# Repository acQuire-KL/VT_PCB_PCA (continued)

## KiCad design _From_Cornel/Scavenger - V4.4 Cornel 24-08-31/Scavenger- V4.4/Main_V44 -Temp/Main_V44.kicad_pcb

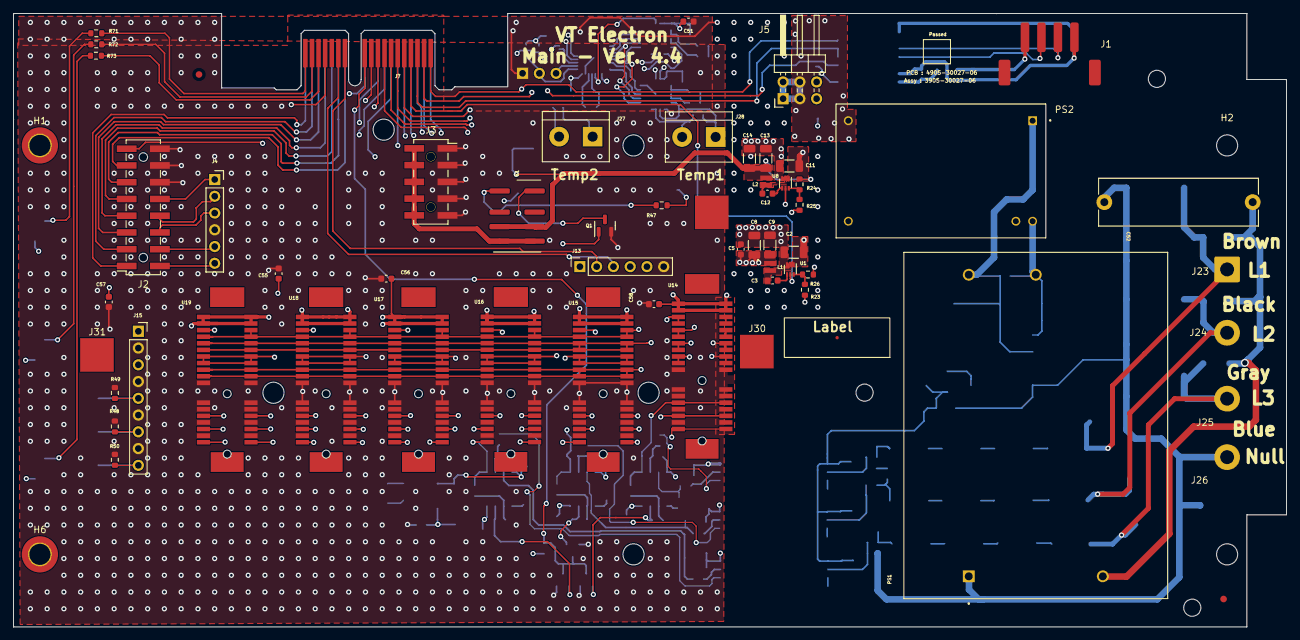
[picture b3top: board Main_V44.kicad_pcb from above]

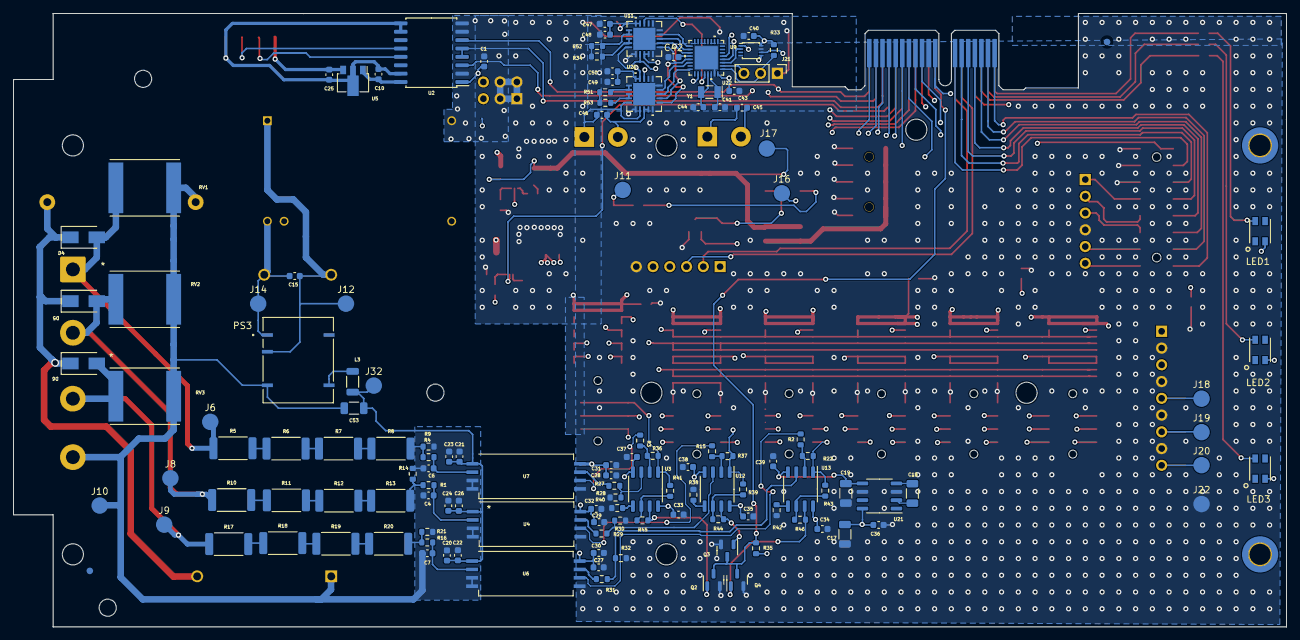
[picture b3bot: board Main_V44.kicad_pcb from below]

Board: 4 copper layers, 193.0 x 93.0 mm, 203 parts (131 on the bottom side), 138 nets.

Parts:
C1, C3, C5, C10, C12, C15, C20, C21, C24, C25, C27, C28, C29, C33, C34, C35, C36, C37, C38, C39, C40, C43, C47, C48, C49, C50, C55, C56, C57, C58: 100n; C_0603_1608Metric
C2, C11, C53: 10uF/16V; C_1206_3216Metric
C4, C6, C7: 1n; C_0603_1608Metric
C8, C9, C13, C14: 22uF/6,3V; C_1206_3216Metric
C17, C18, C19: 10u; C_1206_3216Metric
C22, C23, C26, C30, C31, C32: 1uF; C_0603_1608Metric
C41, C44: 10p; C_0603_1608Metric
C42: 1u; C_0603_1608Metric
C45, C46: 10n; C_0603_1608Metric
C51: 4,7n; C_0603_1608Metric
C52: F862DI224K310ZLH0J; C_Rect_L24.0mm_W7.0mm_P22.50mm_MKT
D4, D5, D6: BYG21M-E3/TR; D_SMA
FID1, FID2, FID3, FID4: Fiducial; Fiducial_1mm_Mask2mm
H1, H6: MountingHole; MountingHole_3.2mm_M3_ISO14580_Pad_TopBottom
H2, H3, H4, H5, H7, H8, H9, H10, H11, H12: MountingHole; MountingHole_3.2mm_M3
J1: Conn_01x04_Male; A2501-SR04-XH4AWB
J2: Conn_02x08_Counter_Clockwise; PinSocket_2x08_P2.54mm_Vertical_SMD_MOD
J3: Conn_02x05_Counter_Clockwise; PinSocket_2x05_P2.54mm_Vertical_SMD
J4, J13: Conn_01x06_Female; PinSocket_1x06_P2.54mm_Vertical
J5: DS1022-2*10RF11x3; PinHeader_2x03_P2.54mm_Horizontal
J6, J8, J9, J10, J11, J12, J14, J16, J17, J18, J19, J20, J22, J32: Conn_01x01_Female; TestPoint_DELTA
J7: Bus_PCI_Express_x1_MOD; BUS_PCIexpress_x1
J15: DS1002-03-1*36131(9); PinSocket_1x09_P2.54mm_Vertical
J21: Conn_01x03_Male; PinHeader_1x03_P2.54mm_Vertical
J23: Conn_01x01_Female; DELTA_SolderWire-1.5sqmm_1x01_D1.7mm_OD3.9mm
J24, J25, J26: Conn_01x01_Female; DELTA_R_SolderWire-1.5sqmm_1x01_D1.7mm_OD3.9mm
J27, J28: Conn_01x02_Female; TerminalBlock_bornier-2_P5.08mm
J29, J30, J31: Conn_01x01_Male; TestPoint_Pad_5.1x5.1mm
K1: FTR-B4GA003Z-B05; Relay_Fujitsu_FTR-B4GA003
L1, L2: 744383130033
L3: CBC3225T220MR; L_1206_3216Metric
LED1, LED2, LED3: CLM2D-GPC-CB0E0793
PS1: RAC15-05SK/480; CONV_RAC15-12SK_480
PS2: THM_10-0511; CONV_THM_10-0511
PS3: NXE2S0505MC-R7; NXE2_SINGLE_SURFACE_MUR
Q1: DTC143T; SOT-23
Q2, Q3, Q4: DTC143E; SOT-23
R1, R4, R16: 10; R_0603_1608Metric
R2, R3, R15, R22, R27, R28, R29, R30, R31, R32, R36, R37, R38, R39, R40, R41, R42, R43, R48, R49, R50: 3k; R_0603_1608Metric
R5, R6, R7, R8, R10, R11, R12, R13, R17, R18, R19, R20: 249k; R_2512_6332Metric
R9, R14, R21: 150; R_0603_1608Metric
R23, R24: 4k7; R_0603_1608Metric
R25: 1k3; R_0603_1608Metric
R26: 1k5; R_0603_1608Metric
R33: 47k; R_0603_1608Metric
R34, R51, R52, R53: 2k 0.1%; R_0603_1608Metric
R35: 1k; R_0603_1608Metric
R44, R45, R46: 15k; R_0603_1608Metric
R47: 47; R_0603_1608Metric
R71, R72, R73: 220; R_0603_1608Metric
RV1, RV2, RV3: MOVS4032V510; MOVS4032V460
TP1: Eticheta
U1, U8: AP62250Z6; SOT-563
U2: ISO3082DW; SOIC-16W_7.5x10.3mm_P1.27mm
U3, U12, U13: LM358; SO-8_3.9x4.9mm_P1.27mm
U4, U6, U7: AMC1400QDWLRQ1
U5: L78L05ACUTR; SOT-89-3
U9: 74LVC2G157; VSSOP-8_2.4x2.1mm_P0.5mm
U11, U20: MAX31865ATP+T; 21-0140L_T2055-5_MXM
U14, U15, U16, U17, U18, U19: 10061913-100CLF
U21: LM2662MX; SO-8_3.9x4.9mm_P1.27mm
U22: MSP430FR2672TRHBR; VQFN32_5X5_TEX
Y1: ECS-.327-6-34B-C-TR; Crystal_SMD_EuroQuartz_EQ161-2Pin_3.2x1.5mm

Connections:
+3V3: C1.1, C5.1, C8.1, C9.1, C17.2, C27.1, C28.1, C29.1, C30.1, C31.1, C32.1, C33.1, C34.1, C35.1, C36.1, C40.1, C43.2, C47.1, C48.1, C49.1, C50.1, C51.2, C55.1, C56.1, C57.1, C58.1, J13.1, J15.1, J16.1, L1.1, LED1.2, LED2.2, LED3.2, R23.2, R33.2, R35.2, U2.1 (Vcc1), U3.8 (v+), U4.8 (VDD2), U6.8 (VDD2), U7.8 (VDD2), U9.8 (VCC), U11.19 (DVDD), U11.20 (VDD), U12.8 (V+), U13.8 (v+), U14.P$A1 (A1), U14.P$A2 (A2), U14.P$B1 (B1), U14.P$B2 (B2), U15.P$A1 (A1), U15.P$A2 (A2), U15.P$B1 (B1), U15.P$B2 (B2), U16.P$A1 (A1), U16.P$A2 (A2), U16.P$B1 (B1), U16.P$B2 (B2), U17.P$A1 (A1), U17.P$A2 (A2), U17.P$B1 (B1), U17.P$B2 (B2), U18.P$A1 (A1), U18.P$A2 (A2), U18.P$B1 (B1), U18.P$B2 (B2), U19.P$A1 (A1), U19.P$A2 (A2), U19.P$B1 (B1), U19.P$B2 (B2), U20.19 (DVDD), U20.20 (VDD), U21.8 (V+), U22.32 (DVCC)
/+3V3_UC: J2.8, J7.A11
/+3V67: C13.1, C14.1, J17.1, K1.3, K1.6, L2.1, R24.2
/+5V: C2.1, C11.1, J5.5, J5.6, J11.1, PS2.13 (+VOUT), R47.2, U1.1 (VIN), U8.1 (VIN), U8.5 (EN)
/-3V3: C19.2, C37.1, C38.1, C39.1, U3.4 (V-), U12.4 (V-), U13.4 (V-), U21.5 (VOUT)
/A+: J1.3, U2.12 (A)
/ADE_Reset: J7.B10, U14.P$B3 (B3), U14.P$B4 (B4), U15.P$B3 (B3), U16.P$B3 (B3), U17.P$B3 (B3), U18.P$B3 (B3), U19.P$B3 (B3)
/Alim: J2.7, J7.A12
/B-: J1.2, U2.13 (B)
/BST1: C3.2, U1.4 (BST)
/BST2: C12.2, U8.4 (BST)
/BT_RTS: J7.B15, U9.6 (~A/B), U22.5 (P1.6)
/BT_RxD: J7.B13, J13.3
/BT_TxD: J7.B12, J13.2
/C+: C18.1, U21.2 (CAP+)
/C-: C18.2, U21.4 (CAP-)
/CS1: U20.13 (*CS), U22.24 (P4.2)
/CS2: U11.13 (*CS), U22.18 (P2.5)
/Enable: J7.B4, U1.5 (EN)
/FB1: R23.1, R26.2, U1.6 (FB)
/FB2: R24.1, R25.2, U8.6 (FB)
/IRQ1: J7.B5, U14.P$A7 (A7), U14.P$A8 (A8)
/IRQ2: U14.P$A5 (A5), U14.P$A6 (A6)
/ISO_Txd: U2.3 (R), U9.1 (A)
/InfoV: J7.B11, Q2.3 (C), Q3.3 (C), Q4.3 (C), R35.1
/L1: Q2.1 (B), R45.1, U3.7
/L2: Q3.1 (B), R44.1, U12.7
/L3: Q4.1 (B), R46.1, U13.7
/LED1: J7.B16, R73.2
/LED2: J7.B17, R72.2
/LED3: J7.B18, R71.2
/MISO: J7.B7, U14.P$B9 (B9), U14.P$B10 (B10)
/MOSI: J7.B8, U14.P$B5 (B5), U14.P$B6 (B6)
/OSC32_IN: C41.1, U22.30 (P2.1/XIN), Y1.1
/OSC32_OUT: C44.1, U22.29 (P2.0/XOUT), Y1.2
/RDY1: U20.18 (*DRDY), U22.26 (P3.5)
/RDY2: U11.18 (*DRDY), U22.28 (P3.6)
/READY: U14.P$A3 (A3), U14.P$A4 (A4)
/RS485_DE: J7.B3, U2.4 (~RE), U2.5 (DE)
/RS485_RxD: J7.B2, U9.5 (Y)
/RS485_TxD: J7.B1, U2.6 (D), U22.4 (P1.5/RXD)
/RxD: J2.6, J7.A13
/SCL: J7.A1, U15.P$A5 (A5), U15.P$A6 (A6), U15.P$B5 (B5), U15.P$B6 (B6), U16.P$A5 (A5), U16.P$A6 (A6), U16.P$B5 (B5), U16.P$B6 (B6), U17.P$A5 (A5), U17.P$A6 (A6), U17.P$B5 (B5), U17.P$B6 (B6), U18.P$A5 (A5), U18.P$A6 (A6), U18.P$B5 (B5), U18.P$B6 (B6), U19.P$A5 (A5), U19.P$A6 (A6), U19.P$B5 (B5), U19.P$B6 (B6)
/SCLK: J7.B6, U14.P$A9 (A9), U14.P$A10 (A10)
/SCLKx: U11.12 (SCLK), U20.12 (SCLK), U22.19 (P2.6)
/SCS: J7.A2, U15.P$A9 (A9), U15.P$A10 (A10), U15.P$B9 (B9), U15.P$B10 (B10), U16.P$A9 (A9), U16.P$A10 (A10), U16.P$B9 (B9), U16.P$B10 (B10), U17.P$A9 (A9), U17.P$A10 (A10), U17.P$B9 (B9), U17.P$B10 (B10), U18.P$A9 (A9), U18.P$A10 (A10), U18.P$B9 (B9), U18.P$B10 (B10), U19.P$A9 (A9), U19.P$A10 (A10), U19.P$B9 (B9), U19.P$B10 (B10)
/SDAT2: J7.A9, U19.P$A7 (A7), U19.P$A8 (A8), U19.P$B7 (B7), U19.P$B8 (B8)
/SDAT3: J7.A8, U18.P$A7 (A7), U18.P$A8 (A8), U18.P$B7 (B7), U18.P$B8 (B8)
/SDAT4: J7.A7, U17.P$A7 (A7), U17.P$A8 (A8), U17.P$B7 (B7), U17.P$B8 (B8)
/SDAT5: J7.A6, U16.P$A7 (A7), U16.P$A8 (A8), U16.P$B7 (B7), U16.P$B8 (B8)
/SDAT6: J7.A5, U15.P$A7 (A7), U15.P$A8 (A8), U15.P$B7 (B7), U15.P$B8 (B8)
/SDAT7: J7.A4, Q1.1 (B)
/SDIx: U11.11 (SDI), U20.11 (SDI), U22.21 (P3.7)
/SDO1: U20.14 (SDO), U22.22 (P4.0)
/SDO2: U11.14 (SDO), U22.17 (P2.4)
/SS: J7.B9, U14.P$B7 (B7), U14.P$B8 (B8)
/SW1: C3.1, L1.2, U1.2 (SW)
/SW2: C12.1, L2.2, U8.2 (SW)
/SYN: J7.A3, U15.P$A3 (A3), U15.P$A4 (A4), U15.P$B4 (B4), U16.P$A3 (A3), U16.P$A4 (A4), U16.P$B4 (B4), U17.P$A3 (A3), U17.P$A4 (A4), U17.P$B4 (B4), U18.P$A3 (A3), U18.P$A4 (A4), U18.P$B4 (B4), U19.P$A3 (A3), U19.P$A4 (A4), U19.P$B4 (B4)
/Temp_Txd: U9.2 (B), U22.3 (P1.4/TXD)
/TxD: J2.5, J7.A14
/U5V_Iso: C15.1, J12.1, PS1.4 (+VOUT), PS2.1 (+VIN(VCC)), PS3.3 (+VIN)
/UCC: C52.1, D4.1 (K), D5.1 (K), D6.1 (K), PS1.2 (VAC_IN(L)(L1))
/UR: D4.2 (A), J6.1, J23.1, R5.1, RV1.1
/UR+: J15.5, J18.1, R36.1, R41.2, R49.1, U3.1, U14.P$A14 (A14), U14.P$B14 (B14), U15.P$A14 (A14), U15.P$B14 (B14), U16.P$A14 (A14), U16.P$B14 (B14), U17.P$A14 (A14), U17.P$B14 (B14), U18.P$A14 (A14), U18.P$B14 (B14), U19.P$A14 (A14), U19.P$B14 (B14)
/UR_Iso: C6.1, R4.2, U7.2 (INP)
/US: D5.2 (A), J8.1, J24.1, R10.1, RV2.1
/US+: J15.7, J19.1, R37.1, R39.2, R48.1, U12.1, U14.P$A16 (A16), U14.P$B16 (B16), U15.P$A16 (A16), U15.P$B16 (B16), U16.P$A16 (A16), U16.P$B16 (B16), U17.P$A16 (A16), U17.P$B16 (B16), U18.P$A16 (A16), U18.P$B16 (B16), U19.P$A16 (A16), U19.P$B16 (B16)
/US_Iso: C4.1, R1.2, U4.2 (INP)
/UT: D6.2 (A), J9.1, J25.1, R17.1, RV3.1
/UT+: J15.9, J20.1, R22.1, R43.2, R50.1, U13.1, U14.P$A18 (A18), U14.P$B18 (B18), U15.P$A18 (A18), U15.P$B18 (B18), U16.P$A18 (A18), U16.P$B18 (B18), U17.P$A18 (A18), U17.P$B18 (B18), U18.P$A18 (A18), U18.P$B18 (B18), U19.P$A18 (A18), U19.P$B18 (B18)
/UT_Iso: C7.1, R16.2, U6.2 (INP)
/VCC2: C10.1, U2.16 (Vcc2), U5.1 (OUT)
/VGSM: J3.6, J3.7, J3.8, J3.9, J3.10, K1.4, K1.5
/Vin: C25.1, J1.1, U5.3 (IN)
/Vopto: C20.1, C21.1, C22.1, C23.1, C24.1, C26.1, C53.1, J32.1, L3.2, U4.1 (VDD1), U6.1 (VDD1), U7.1 (VDD1)
/iUR+: R27.1, R28.2, U3.3 (+)
/iUR-: R3.2, U7.6 (OUTN)
/iUS+: R29.1, R30.2, U12.3 (+)
/iUS-: R15.2, U4.6 (OUTN)
/iUT+: R31.1, R32.2, U13.3 (+)
/iUT-: R2.2, U6.6 (OUTN)
/uDCD: J2.2, J7.A17
/uDTR: J2.1, J7.A18
/uPWRKEY: J2.4, J7.A15
/uStatus: J2.3, J7.A16
Earth: C10.2, C25.2, J1.4, U2.9 (GND2), U2.10 (GND2), U2.15 (GND2), U5.2 (GND)
GND: C1.2, C2.2, C5.2, C8.2, C9.2, C11.2, C13.2, C14.2, C17.1, C19.1, C27.2, C28.2, C29.2, C30.2, C31.2, C32.2, C33.2, C34.2, C35.2, C36.2, C37.2, C38.2, C39.2, C40.2, C41.2, C42.1, C43.1, C44.2, C47.2, C48.2, C49.2, C50.2, C51.1, C55.2, C56.2, C57.2, C58.2, J2.14, J2.15, J2.16, J3.1, J3.2, J3.3, J3.4, J3.5, J4.4, J5.1, J5.2, J5.3, J5.4, J7.A10, J13.6, J15.2, J15.4, J15.6, J15.8, J21.1, J22.1, PS2.12 (-VOUT), Q1.2 (E), Q2.2 (E), Q3.2 (E), Q4.2 (E), R25.1, R26.1, R28.1, R30.1, R32.1, R38.2, R40.2, R42.2, R48.2, R49.2, R50.2, U1.3 (GND), U2.2 (GND1), U2.7 (GND1), U2.8 (GND1), U4.5 (GND2), U6.5 (GND2), U7.5 (GND2), U8.3 (GND), U9.7 (~G), U11.6 (FORCE2), U11.10 (GND2), U11.15 (DGND), U11.16 (GND1), U11.21 (EP), U14.P$A11 (A11), U14.P$A12 (A12), U14.P$A13 (A13), U14.P$A15 (A15), U14.P$A17 (A17), U14.P$B11 (B11), U14.P$B12 (B12), U14.P$B13 (B13), U14.P$B15 (B15), U14.P$B17 (B17), U15.P$A11 (A11), U15.P$A12 (A12), U15.P$A13 (A13), U15.P$A15 (A15), U15.P$A17 (A17), U15.P$B11 (B11), U15.P$B12 (B12), U15.P$B13 (B13), U15.P$B15 (B15), U15.P$B17 (B17), U16.P$A11 (A11), U16.P$A12 (A12), U16.P$A13 (A13), U16.P$A15 (A15), U16.P$A17 (A17), U16.P$B11 (B11), U16.P$B12 (B12), U16.P$B13 (B13), U16.P$B15 (B15), U16.P$B17 (B17), U17.P$A11 (A11), U17.P$A12 (A12), U17.P$A13 (A13), U17.P$A15 (A15), U17.P$A17 (A17), U17.P$B11 (B11), U17.P$B12 (B12), U17.P$B13 (B13), U17.P$B15 (B15), U17.P$B17 (B17), U18.P$A11 (A11), U18.P$A12 (A12), U18.P$A13 (A13), U18.P$A15 (A15), U18.P$A17 (A17), U18.P$B11 (B11), U18.P$B12 (B12), U18.P$B13 (B13), U18.P$B15 (B15), U18.P$B17 (B17), U19.P$A11 (A11), U19.P$A12 (A12), U19.P$A13 (A13), U19.P$A15 (A15), U19.P$A17 (A17), U19.P$B11 (B11), U19.P$B12 (B12), U19.P$B13 (B13), U19.P$B15 (B15), U19.P$B17 (B17), U20.6 (FORCE2), U20.10 (GND2), U20.15 (DGND), U20.16 (GND1), U20.21 (EP), U21.3 (GND), U21.6 (LV), U22.31 (DVSS), U22.33 (PAD)
GND1: C15.2, J14.1, PS1.3 (-VOUT), PS2.24 (-VIN(GND)), PS3.1 (-VIN)
GNDS: C4.2, C6.2, C7.2, C20.2, C21.2, C22.2, C23.2, C24.2, C26.2, C52.2, C53.2, J10.1, J26.1, PS1.1 (VAC_IN(N)(L2)), PS3.7 (-VOUT), R9.2, R14.2, R21.2, RV1.2, RV2.2, RV3.2, U4.3 (INN), U4.4 (GND1), U6.3 (INN), U6.4 (GND1), U7.3 (INN), U7.4 (GND1)
unnamed: C42.2, U22.20 (VREG)
unnamed: C45.1, J27.2, U11.8 (RTDIN-), U11.9 (FORCE-)
unnamed: C45.2, J27.1, U11.5 (FORCE+), U11.7 (RTDIN+)
unnamed: C46.1, J28.2, U20.8 (RTDIN-), U20.9 (FORCE-)
unnamed: C46.2, J28.1, U20.5 (FORCE+), U20.7 (RTDIN+)
unnamed: J2.9, J4.6
unnamed: J2.10, J4.5
unnamed: J2.11, J4.3
unnamed: J2.12, J4.2
unnamed: J2.13, J4.1
unnamed: J21.2, R33.1, U22.1 (RST)
unnamed: J21.3, U22.2 (TEST)
unnamed: K1.1, R47.1
unnamed: K1.8, Q1.3 (C)
unnamed: L3.1, PS3.8 (+VOUT)
unnamed: LED1.4, R71.1
unnamed: LED2.4, R72.1
unnamed: LED3.4, R73.1
unnamed: R1.1, R13.2, R14.1
unnamed: R2.1, R22.2, U13.2 (-)
unnamed: R3.1, R36.2, U3.2 (-)
unnamed: R4.1, R8.2, R9.1
unnamed: R5.2, R6.1
unnamed: R6.2, R7.1
unnamed: R7.2, R8.1
unnamed: R10.2, R11.1
unnamed: R11.2, R12.1
unnamed: R12.2, R13.1
unnamed: R15.1, R37.2, U12.2 (-)
unnamed: R16.1, R20.2, R21.1
unnamed: R17.2, R18.1
unnamed: R18.2, R19.1
unnamed: R19.2, R20.1
unnamed: R27.2, U7.7 (OUTP)
unnamed: R29.2, U4.7 (OUTP)
unnamed: R31.2, U6.7 (OUTP)
unnamed: R34.1, U11.3 (REFIN-), U11.4 (ISENSOR)
unnamed: R34.2, R52.1
unnamed: R38.1, U12.5 (+)
unnamed: R39.1, R44.2, U12.6 (-)
unnamed: R40.1, U3.5 (+)
unnamed: R41.1, R45.2, U3.6 (-)
unnamed: R42.1, U13.5 (+)
unnamed: R43.1, R46.2, U13.6 (-)
unnamed: R51.1, U20.1 (BIAS), U20.2 (REFIN+)
unnamed: R51.2, R53.2
unnamed: R52.2, U11.1 (BIAS), U11.2 (REFIN+)
unnamed: R53.1, U20.3 (REFIN-), U20.4 (ISENSOR)

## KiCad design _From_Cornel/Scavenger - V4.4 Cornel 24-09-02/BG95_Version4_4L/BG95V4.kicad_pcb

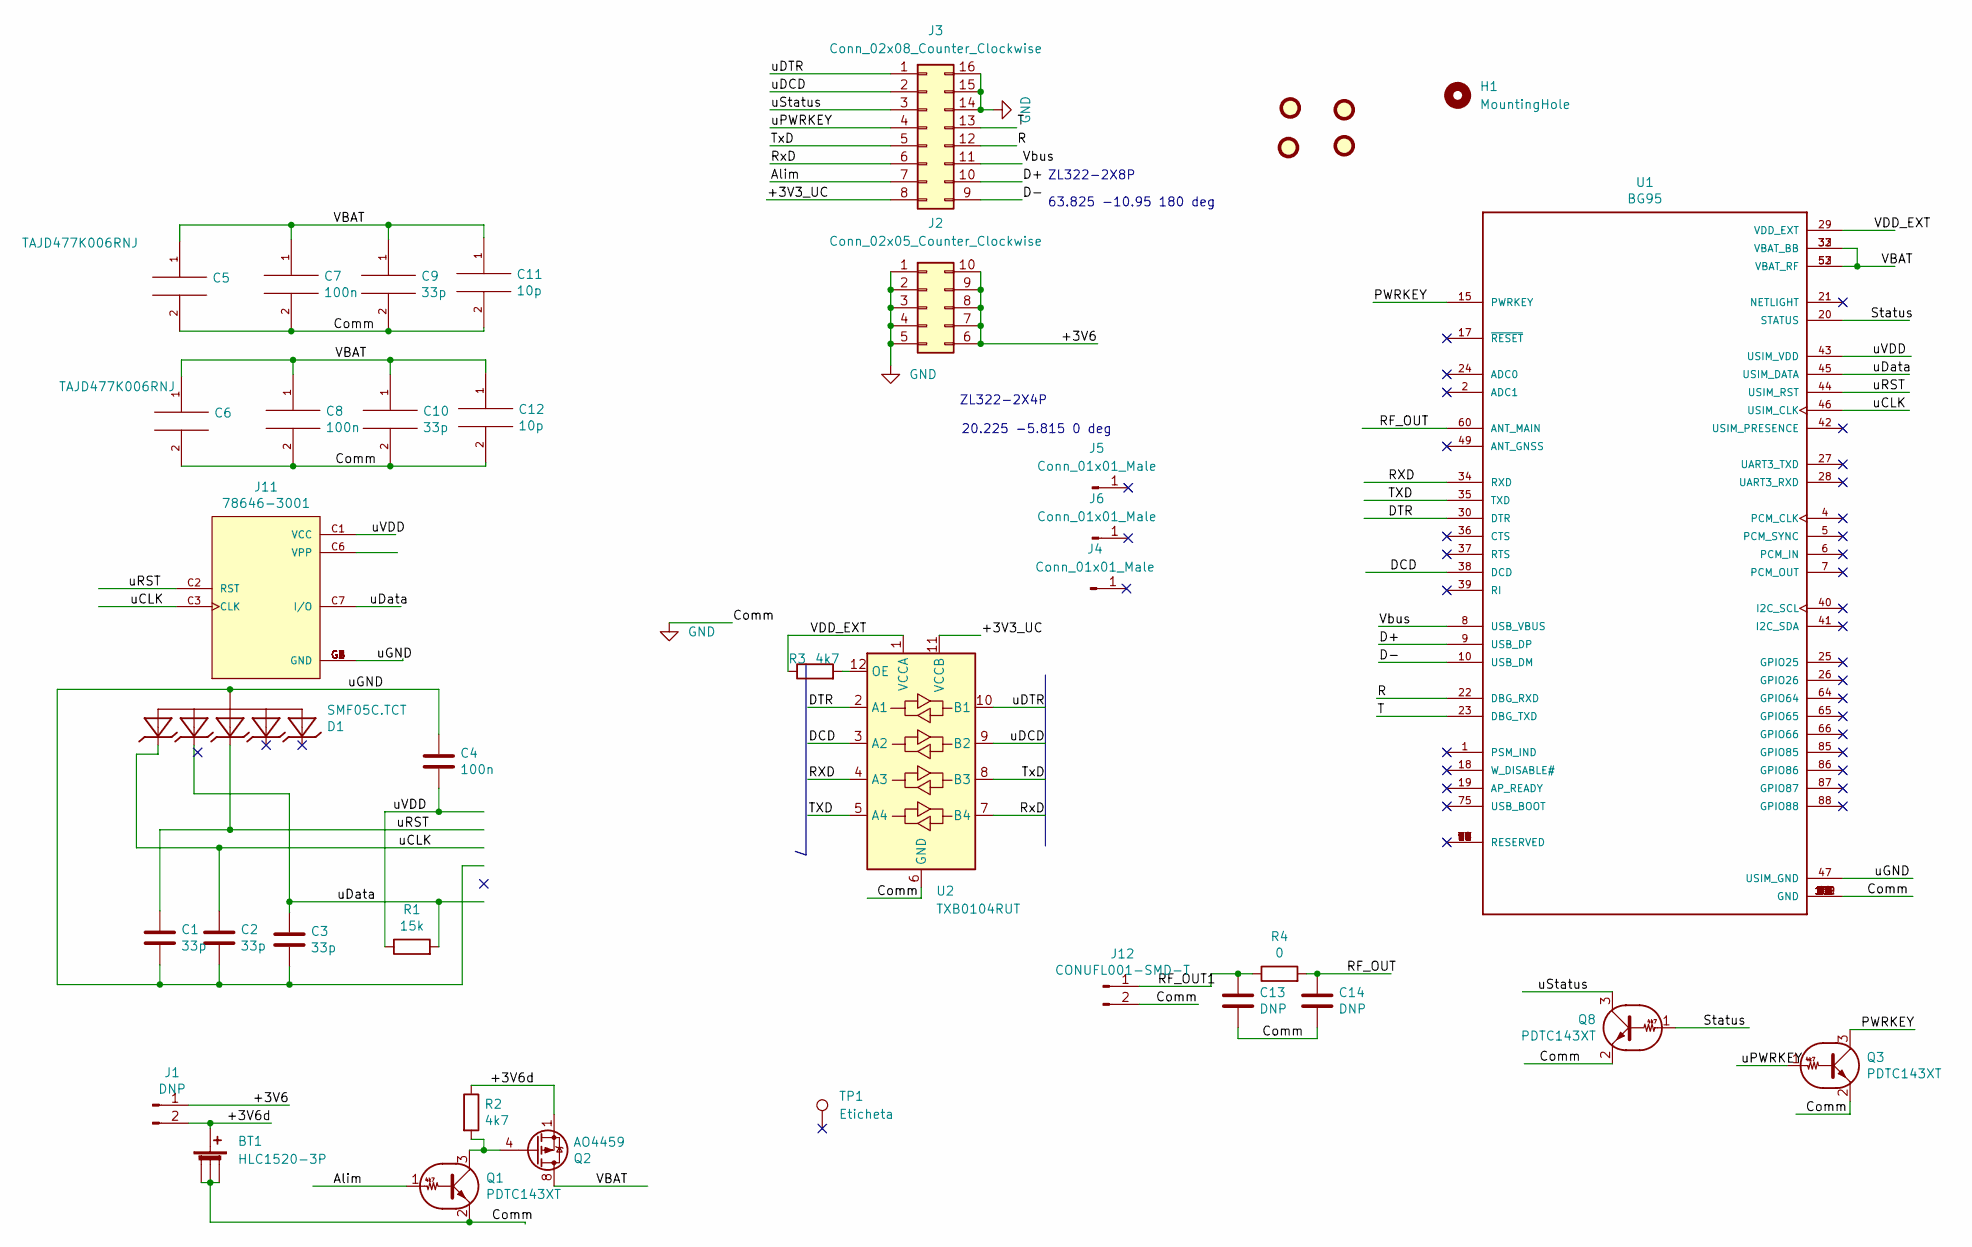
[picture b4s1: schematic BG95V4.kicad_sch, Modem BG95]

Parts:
BT1: HLC1520-3P
C1, C2, C3: 33p; C_0603_1608Metric
C4: 100n; C_0603_1608Metric
C5, C6: TAJD477K006RNJ; CP_EIA-7361-38_AVX-V_Pad2.18x3.30mm_HandSolder
C7, C8: 100n; C_0603_1608Metric_Pad1.05x0.95mm_HandSolder
C9, C10: 33p; C_0603_1608Metric_Pad1.05x0.95mm_HandSolder
C11, C12: 10p; C_0603_1608Metric_Pad1.05x0.95mm_HandSolder
C13, C14: DNP; C_0603_1608Metric
D1: SMF05C.TCT; SC70-6
FID1, FID2, FID3, FID4: Fiducial; Fiducial_1mm_Mask2mm
H1: MountingHole; MountingHole_2.5mm Simpla
J1: DNP; PinHeader_1x02_P2.54mm_Vertical
J2: Conn_02x05_Counter_Clockwise; PinHeader_2x05_P2.54mm_Vertical_SMD_MOD
J3: Conn_02x08_Counter_Clockwise; PinHeader_2x08_P2.54mm_Vertical_SMD_MOD
J4, J5, J6: Conn_01x01_Male; TestPoint_Pad_5.1x5.1mm
J11: 78646-3001; MOLEX_78646-3001; DIGI-KEY_PART_NUMBER WM9364CT-ND
J12: CONUFL001-SMD-T; U.FL_Molex_MCRF_73412-0110_Vertical
Q1, Q3, Q8: PDTC143XT; SOT-23
Q2: AO4459; SOIC-8_3.9x4.9mm_P1.27mm
R1: 15k; R_0603_1608Metric
R2, R3: 4k7; R_0603_1608Metric
R4: 0; R_0603_1608Metric
TP1: Eticheta
U1: BG95; XCVR_BG95M3LA-64-SGNS
U2: TXB0104RUT; Texas_R_PUQFN-N12

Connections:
/+3V3_UC: J3.8, U2.11 (VCCB)
/+3V6: J1.1, J2.6, J2.7, J2.8, J2.9, J2.10
/+3V6d: BT1.1 (+), J1.2, Q2.1 (S), Q2.2 (S), Q2.3 (S), R2.1
/Alim: J3.7, Q1.1 (B)
/D+: J3.10, U1.9 (USB_DP)
/D-: J3.9, U1.10 (USB_DM)
/DCD: U1.38 (DCD), U2.3 (A2)
/DTR: U1.30 (DTR), U2.2 (A1)
/PWRKEY: Q3.3 (C), U1.15 (PWRKEY)
/R: J3.12, U1.22 (DBG_RXD)
/RF_OUT: C14.1, R4.2, U1.60 (ANT_MAIN)
/RF_OUT1: C13.1, J12.1, R4.1
/RXD: U1.34 (RXD), U2.4 (A3)
/RxD: J3.6, U2.7 (B4)
/Status: Q8.1 (B), U1.20 (STATUS)
/T: J3.13, U1.23 (DBG_TXD)
/TXD: U1.35 (TXD), U2.5 (A4)
/TxD: J3.5, U2.8 (B3)
/VBAT: C5.1, C6.1, C7.1, C8.1, C9.1, C10.1, C11.1, C12.1, Q2.5 (D), Q2.6 (D), Q2.7 (D), Q2.8 (D), U1.32 (VBAT_BB), U1.33 (VBAT_BB), U1.52 (VBAT_RF), U1.53 (VBAT_RF)
/VDD_EXT: R3.1, U1.29 (VDD_EXT), U2.1 (VCCA)
/Vbus: J3.11, U1.8 (USB_VBUS)
/uCLK: C2.1, D1.6, J11.C3 (CLK), U1.46 (USIM_CLK)
/uDCD: J3.2, U2.9 (B2)
/uDTR: J3.1, U2.10 (B1)
/uData: C3.1, D1.5, J11.C7 (I/O), R1.2, U1.45 (USIM_DATA)
/uGND: C1.2, C2.2, C3.2, C4.1, D1.2, J11.C5 (GND), J11.G1 (GND), J11.G2 (GND), J11.G3 (GND), J11.G4 (GND), J11.G5 (GND), J11.G6 (GND), U1.47 (USIM_GND)
/uPWRKEY: J3.4, Q3.1 (B)
/uRST: C1.1, D1.4, J11.C2 (RST), U1.44 (USIM_RST)
/uStatus: J3.3, Q8.3 (C)
/uVDD: C4.2, J11.C1 (VCC), R1.1, U1.43 (USIM_VDD)
GND: BT1.2 (-), BT1.3 (-), BT1.4 (-), C5.2, C6.2, C7.2, C8.2, C9.2, C10.2, C11.2, C12.2, C13.2, C14.2, J2.1, J2.2, J2.3, J2.4, J2.5, J3.14, J3.15, J3.16, J12.2, Q1.2 (E), Q3.2 (E), Q8.2 (E), U1.3 (GND), U1.31 (GND), U1.48 (GND), U1.50 (GND), U1.54 (GND), U1.55 (GND), U1.58 (GND), U1.59 (GND), U1.61 (GND), U1.62 (GND), U1.67 (GND), U1.68 (GND), U1.69 (GND), U1.70 (GND), U1.71 (GND), U1.72 (GND), U1.73 (GND), U1.74 (GND), U1.79 (GND), U1.80 (GND), U1.81 (GND), U1.82 (GND), U1.89 (GND), U1.90 (GND), U1.91 (GND), U1.100 (GND), U1.101 (GND), U1.102 (GND), U2.6 (GND)
unnamed: Q1.3 (C), Q2.4 (G), R2.2
unnamed: R3.2, U2.12 (OE)

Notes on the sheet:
ZL322-2X8P
20.225 -5.815 0 deg
ZL322-2X4P
63.825 -10.95 180 deg

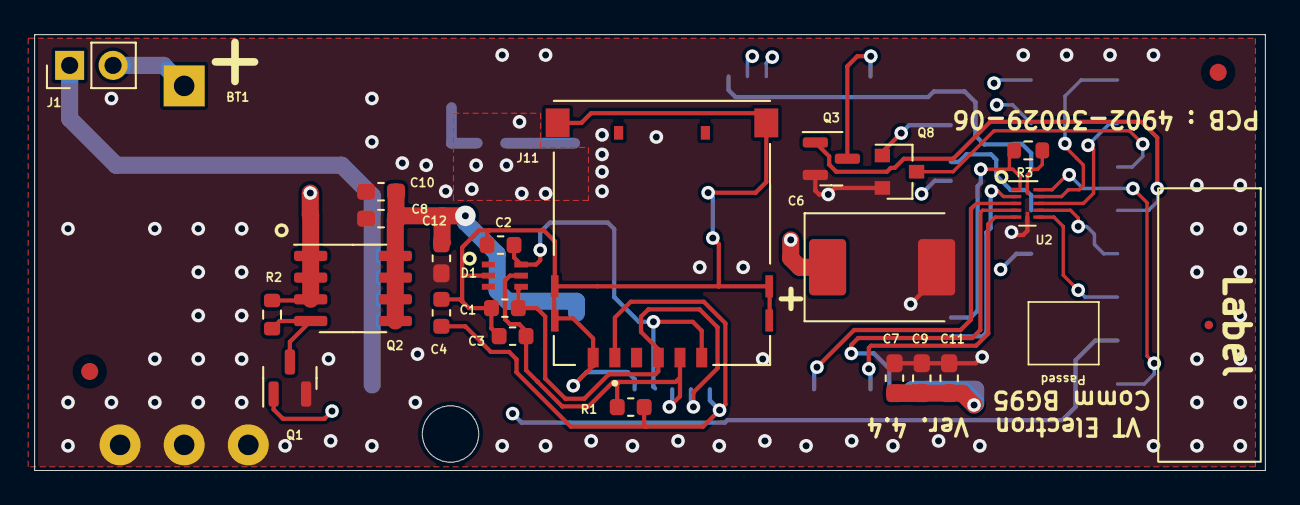
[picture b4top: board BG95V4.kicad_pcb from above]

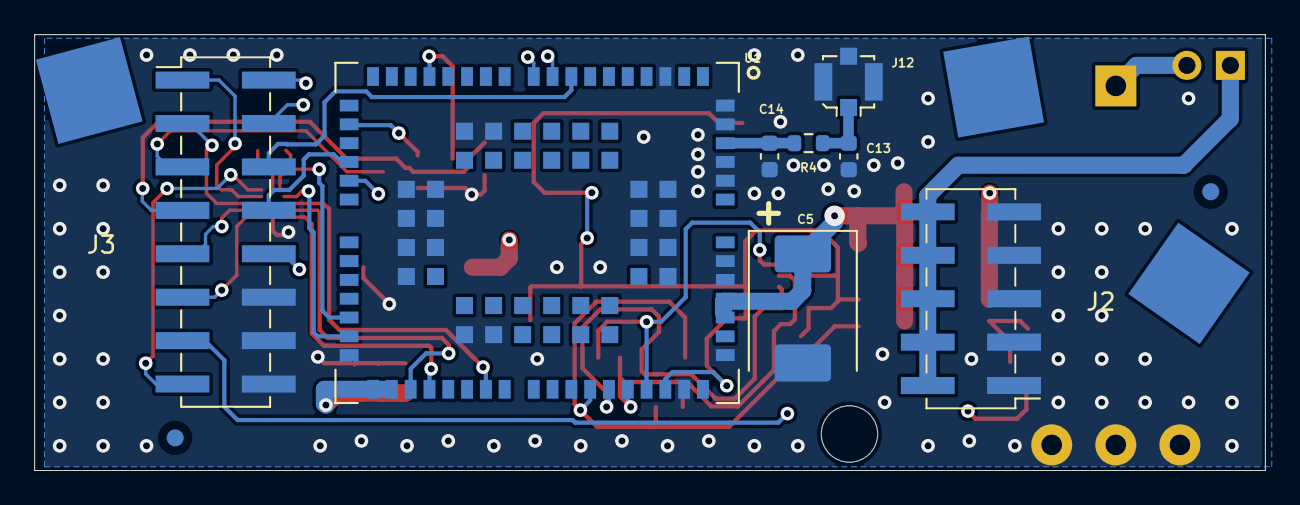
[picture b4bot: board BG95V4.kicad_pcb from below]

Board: 4 copper layers, 72.0 x 25.5 mm, 40 parts (13 on the bottom side), 33 nets.
